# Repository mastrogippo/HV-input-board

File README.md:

## EVSE High voltage input circuit test

[Writeup and pics here](http://www.mastrogippo.it/2019/08/first-prototype-and-test-hardware/)

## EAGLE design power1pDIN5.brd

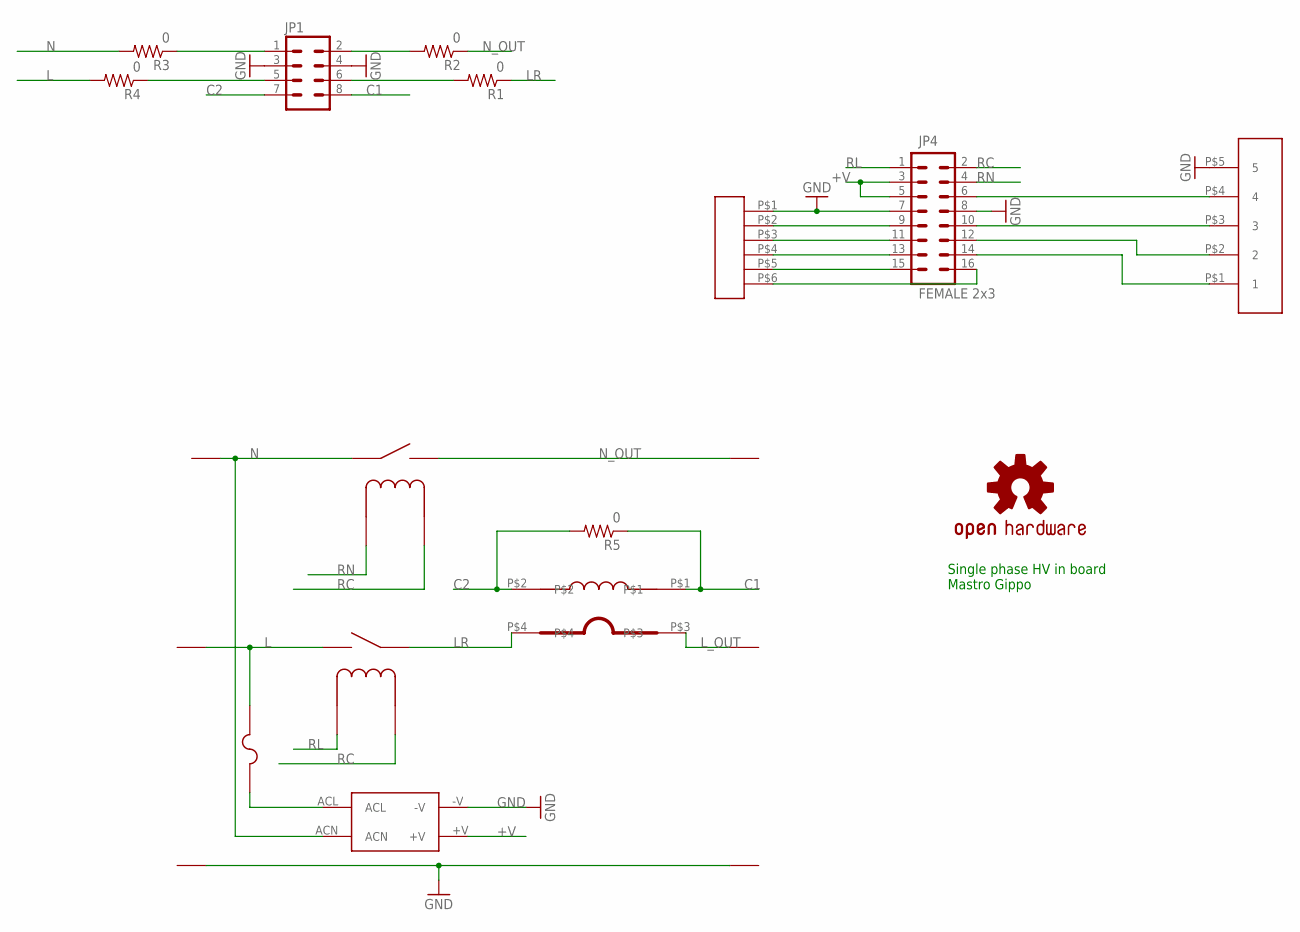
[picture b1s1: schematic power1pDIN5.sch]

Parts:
JP1: M04X2; 2X4
JP4: FEMALE 2x3; 2X8
R1, R2, R3, R4, R5: 0; 0805
U$1, U$2: T9S; T9SSOLAR
U$3, U$4, U$5, U$6, U$9, U$10: PLH5_1; PLH5
U$7: FUSE-0ZRE0008FF1C; 0ZRE0008FF1C
U$8: CSE187L
U$11: PTSA5
U$12: IRM-10-12; ACDCMEANWELL
U$13: OSHW-LOGOM; OSHW-LOGO-M
U$14: PTSA6

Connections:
+V: JP4.3, JP4.5, U$12.+V
C1: JP1.8, R5.1, U$8.P$1
C2: JP1.7, R5.2, U$8.P$2
GND: JP1.3, JP1.4, JP4.7, JP4.8, U$9.P$1, U$9.P$2, U$10.P$1, U$10.P$2, U$11.P$5 (5), U$12.-V, U$14.P$1
L: R4.2, U$2.TL1 (TL), U$2.TL2 (TL), U$4.P$1, U$4.P$2, U$7.P$2 (2)
LR: R1.1, U$2.TR1 (TR), U$2.TR2 (TR), U$8.P$4
L_OUT: U$6.P$1, U$6.P$2, U$8.P$3
N: R3.2, U$1.TR1 (TR), U$1.TR2 (TR), U$3.P$1, U$3.P$2, U$12.ACN
unnamed: JP1.2, R2.2
unnamed: JP4.15, U$14.P$5
unnamed: JP4.13, U$14.P$4
unnamed: JP4.11, U$14.P$3
unnamed: JP1.6, R1.2
unnamed: JP1.1, R3.1
unnamed: JP4.9, U$14.P$2
unnamed: JP4.16, U$14.P$6
unnamed: JP1.5, R4.1
unnamed: JP4.6, U$11.P$4 (4)
unnamed: JP4.10, U$11.P$3 (3)
unnamed: JP4.12, U$11.P$2 (2)
unnamed: U$7.P$1 (1), U$12.ACL
unnamed: JP4.14, U$11.P$1 (1)
N_OUT: R2.1, U$1.TL1 (TL), U$1.TL2 (TL), U$5.P$1, U$5.P$2
RC: JP4.2, U$1.C1, U$2.C2
RL: JP4.1, U$2.C1
RN: JP4.4, U$1.C2

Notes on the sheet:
Single phase HV in board Mastro Gippo

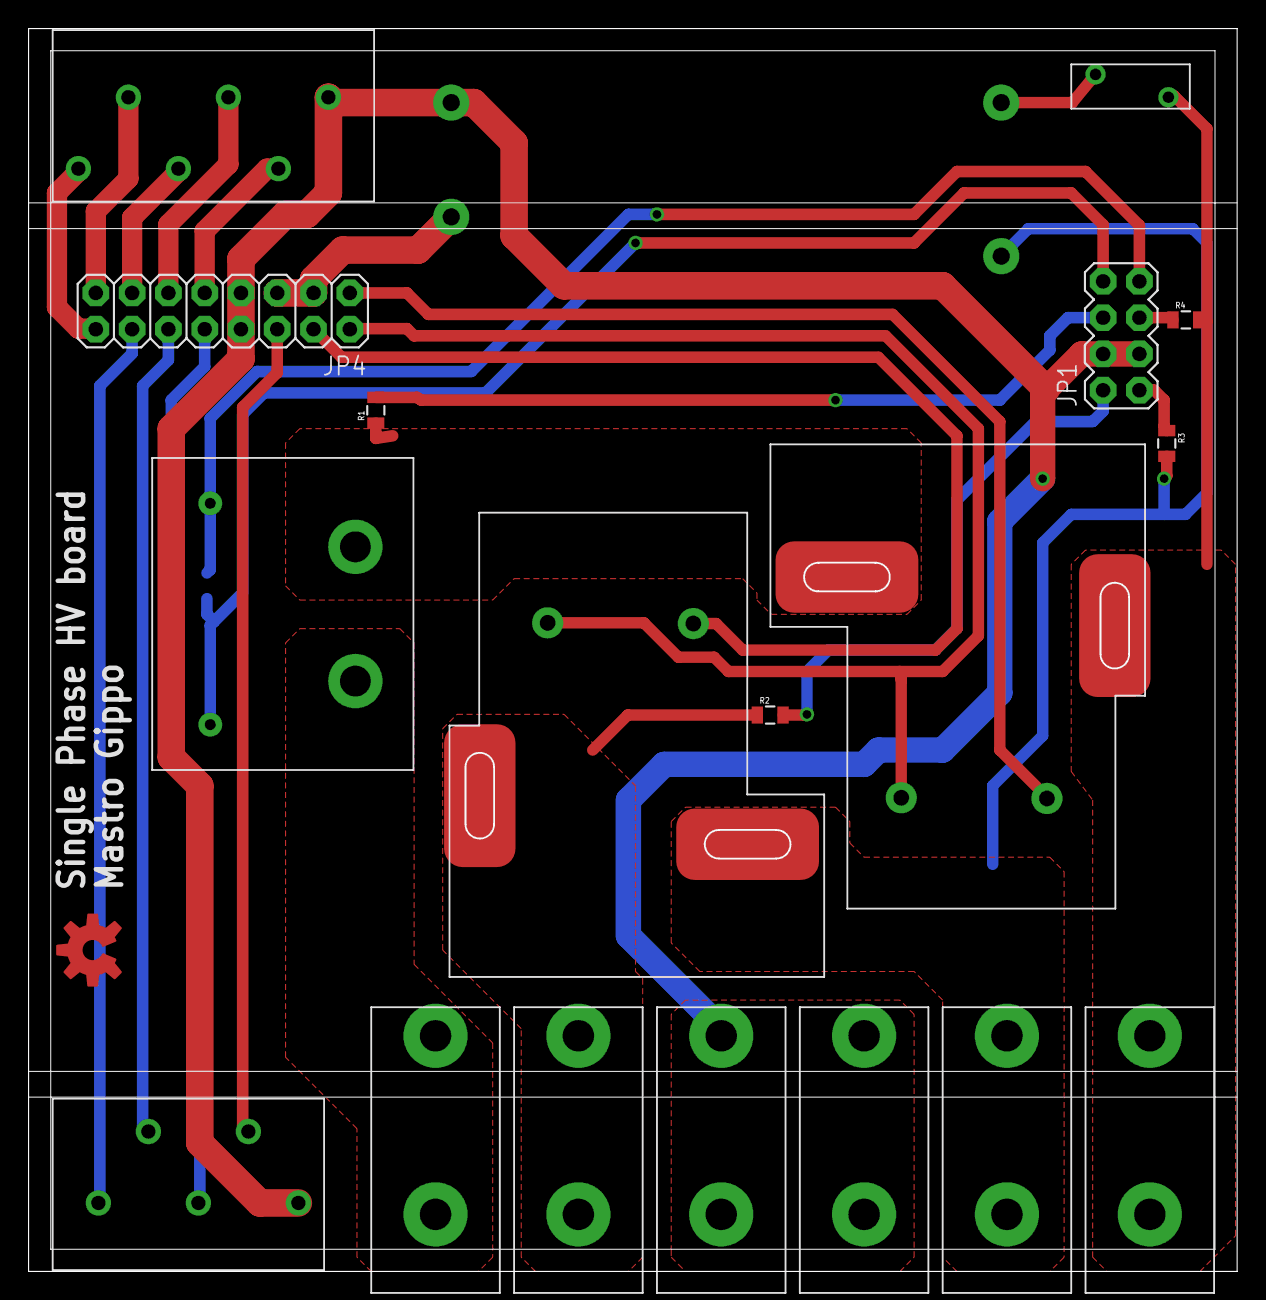
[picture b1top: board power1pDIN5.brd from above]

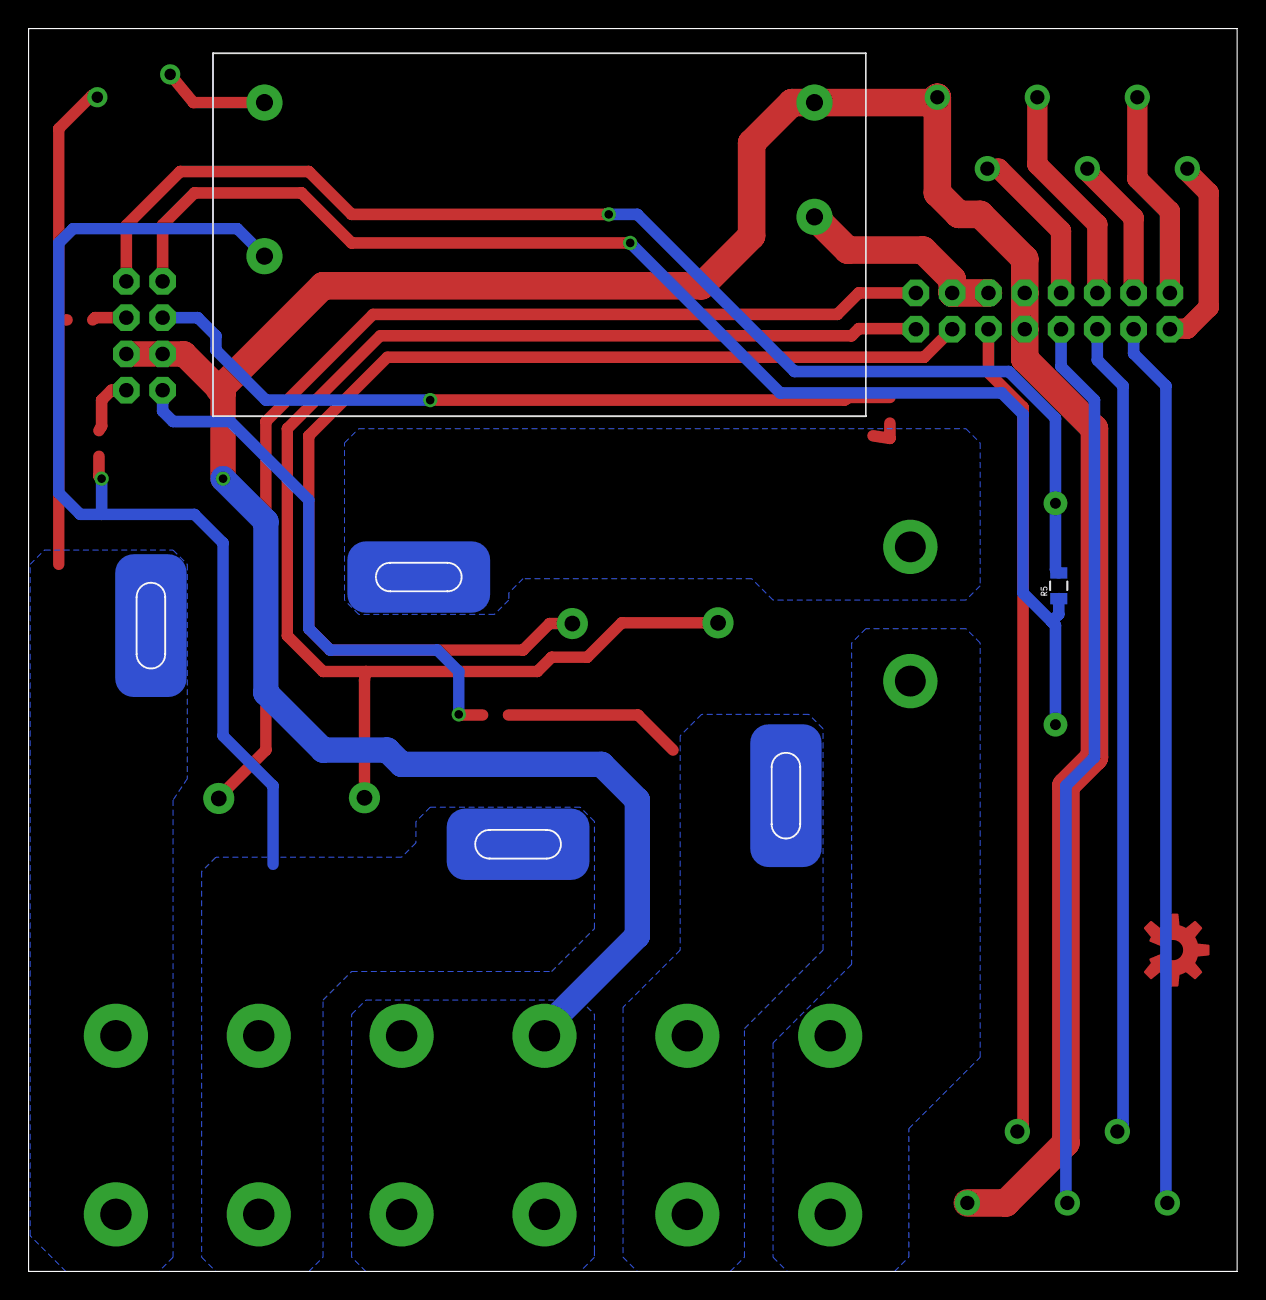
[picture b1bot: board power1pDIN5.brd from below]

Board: 2 copper layers, 84.5 x 86.9 mm, 21 parts (3 on the bottom side), 26 nets.

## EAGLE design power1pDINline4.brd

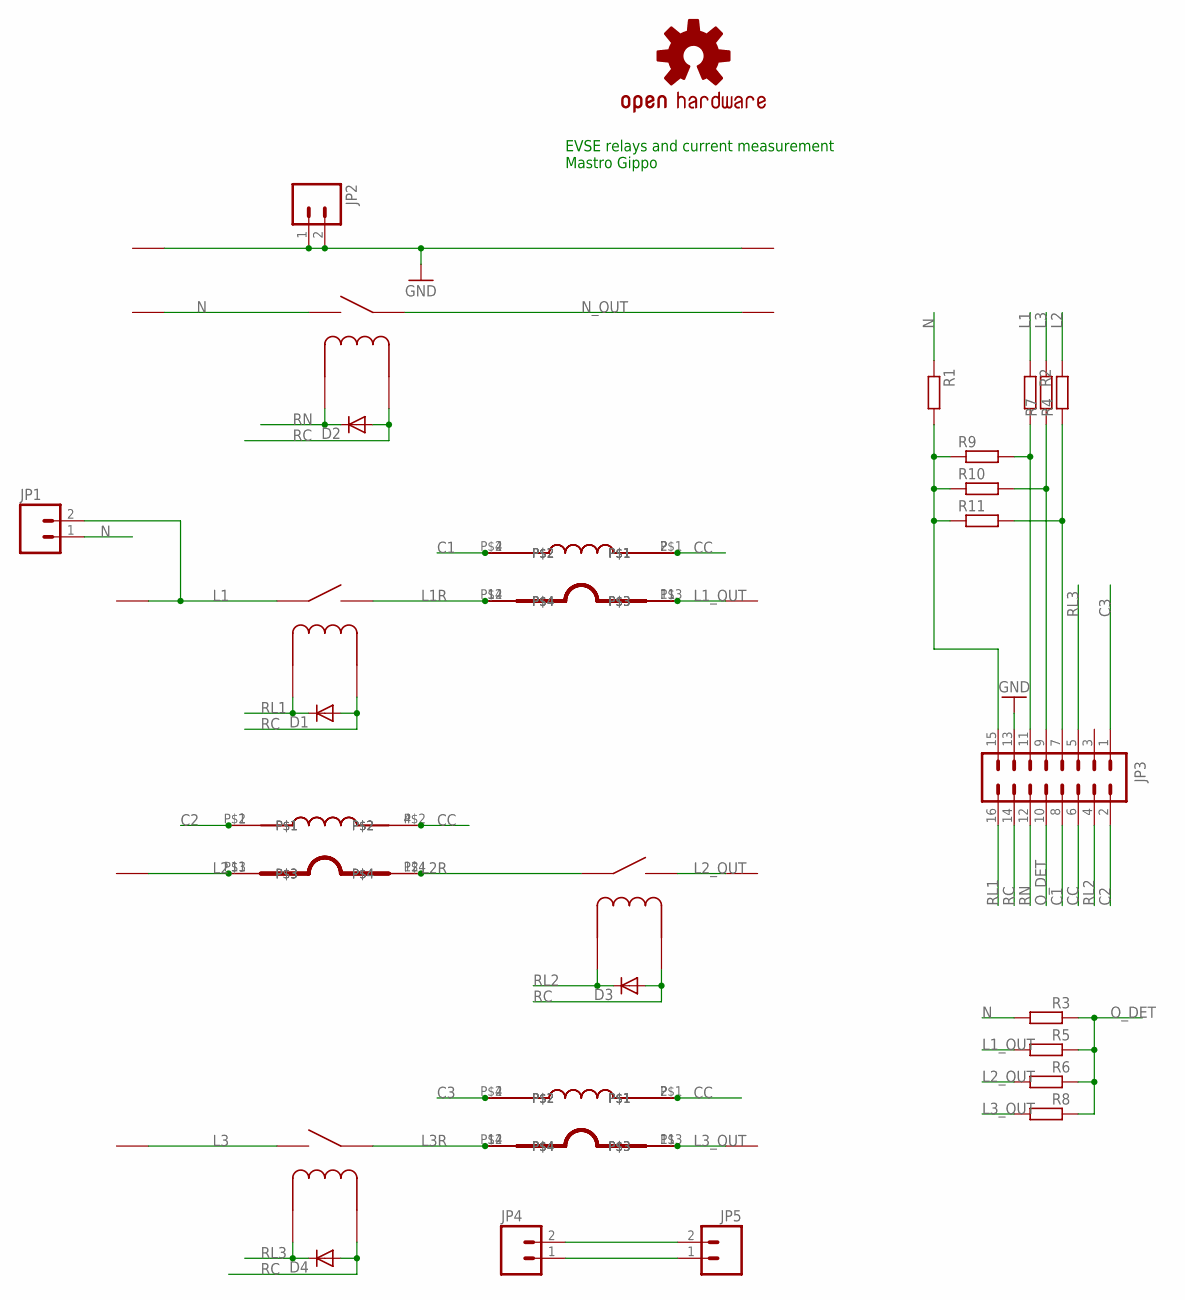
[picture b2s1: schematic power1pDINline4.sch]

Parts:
D1, D2, D3, D4: DIODE-DO-214AC; DO-214AC
JP1, JP2, JP4, JP5: M025MM; SCREWTERMINAL-5MM-2
JP3: M08X2; 2X8
R1, R2, R3, R4, R5, R6, R7, R8: R-EU_0207_10; 0207/10
R9, R10, R11: R-EU_M0805; M0805
U$1, U$2, U$12, U$17: T9S; T9SSOLAR
U$3, U$4, U$5, U$6, U$7, U$9, U$10, U$11, U$14, U$15: PLH5_1; PLH5
U$8, U$20, U$22: CSE187L
U$16, U$18, U$19: PB0025NL; PILSA_CURR_MIN
U$21: OSHW-LOGOL; OSHW-LOGO-L

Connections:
C1: JP3.8, U$8.P$2, U$18.4
C2: JP3.2, U$19.2, U$22.P$1
C3: JP3.1, U$16.4, U$20.P$2
CC: JP3.6, U$8.P$1, U$16.2, U$18.2, U$19.4, U$20.P$1, U$22.P$2
GND: JP2.1, JP2.2, JP3.13, U$9.P$1, U$9.P$2, U$10.P$1, U$10.P$2
L1: JP1.2, R2.1, U$2.TR1 (TR), U$2.TR2 (TR), U$4.P$1, U$4.P$2
L1R: U$2.TL1 (TL), U$2.TL2 (TL), U$8.P$4, U$18.12
L1_OUT: R5.2, U$6.P$1, U$6.P$2, U$8.P$3, U$18.11
L2: R4.2, U$7.P$1, U$7.P$2, U$19.11, U$22.P$3
L2R: U$12.TR1 (TR), U$12.TR2 (TR), U$19.12, U$22.P$4
L2_OUT: R6.2, U$11.P$1, U$11.P$2, U$12.TL1 (TL), U$12.TL2 (TL)
L3: R7.2, U$14.P$1, U$14.P$2, U$17.TL1 (TL), U$17.TL2 (TL)
L3R: U$16.12, U$17.TR1 (TR), U$17.TR2 (TR), U$20.P$4
L3_OUT: R8.2, U$15.P$1, U$15.P$2, U$16.11, U$20.P$3
N: JP1.1, R1.1, R3.2, U$1.TL1 (TL), U$1.TL2 (TL), U$3.P$1, U$3.P$2
unnamed: JP3.9, R7.1, R10.2
unnamed: JP4.1, JP5.1
unnamed: JP4.2, JP5.2
unnamed: JP3.11, R2.2, R9.2
unnamed: JP3.15, R1.2, R9.1, R10.1, R11.1
unnamed: JP3.7, R4.1, R11.2
N_OUT: U$1.TR1 (TR), U$1.TR2 (TR), U$5.P$1, U$5.P$2
O_DET: JP3.10, R3.1, R5.1, R6.1, R8.1
RC: D1.A, D2.A, D3.A, D4.A, JP3.14, U$1.C2, U$2.C1, U$12.C1, U$17.C2
RL1: D1.C, JP3.16, U$2.C2
RL2: D3.C, JP3.4, U$12.C2
RL3: D4.C, JP3.5, U$17.C1
RN: D2.C, JP3.12, U$1.C1

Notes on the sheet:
EVSE relays and current measurement Mastro Gippo

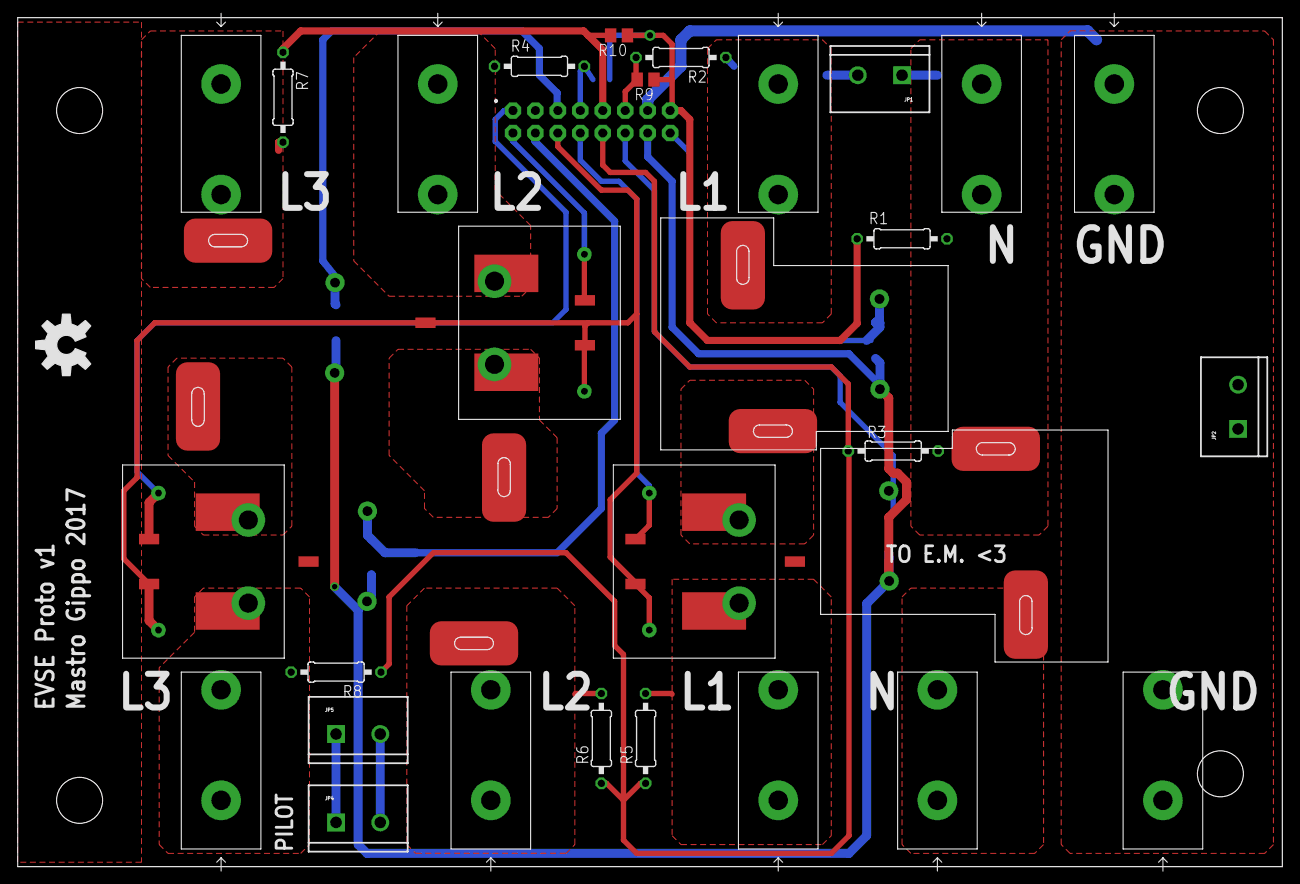
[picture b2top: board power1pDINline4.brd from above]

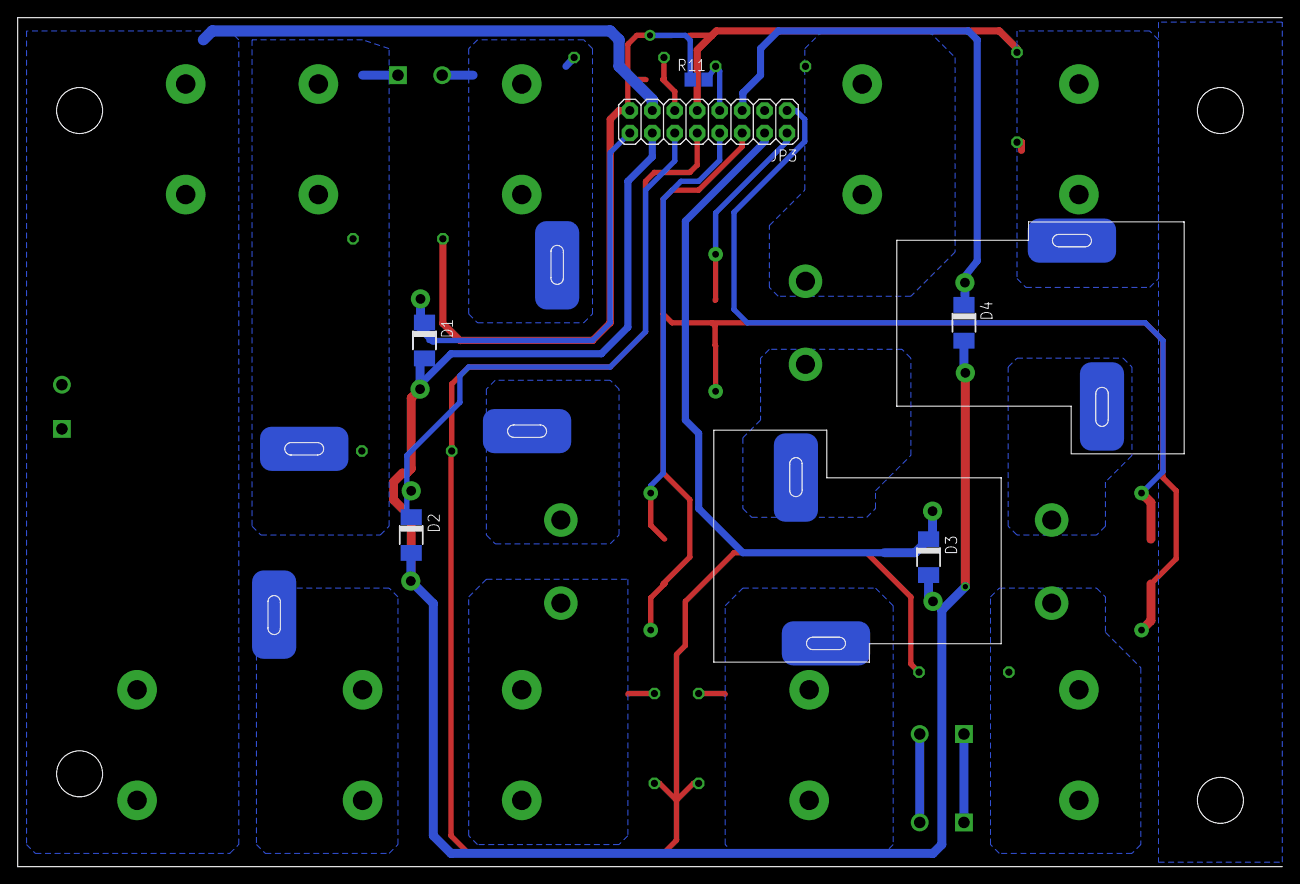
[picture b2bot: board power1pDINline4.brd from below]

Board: 2 copper layers, 142.9 x 95.9 mm, 41 parts (8 on the bottom side), 28 nets.

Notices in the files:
parts and their libraries:
SparkFun-Connectors: Licensing: CC v3.0 Share-Alike You are welcome to use this library for commercial purposes.
SparkFun-Connectors: Licensing: Creative Commons ShareAlike 4.0 International - https://creativecommons.org/licenses/by-sa/4.0
